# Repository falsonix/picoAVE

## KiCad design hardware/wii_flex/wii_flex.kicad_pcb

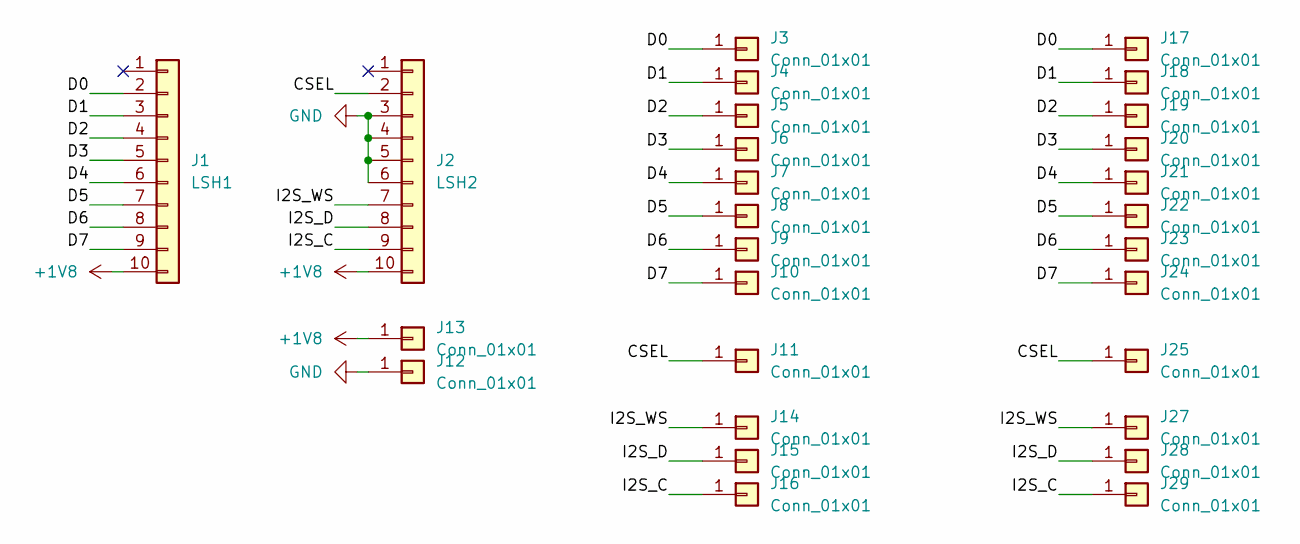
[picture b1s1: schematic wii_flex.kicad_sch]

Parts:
J1: LSH1; PinHeader_1x10_P2.54mm_Vertical
J2: LSH2; PinHeader_1x10_P2.54mm_Vertical
J3, J4, J5, J6, J7, J8, J9, J10, J11, J14, J15, J16, J17, J18, J19, J20, J21, J22, J23, J24, J25, J27, J28, J29: Conn_01x01; wii_pin
J12, J13: Conn_01x01; TestPoint_Pad_2.0x2.0mm

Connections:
+1V8: J1.10, J2.10, J13.1
/CSEL: J2.2, J11.1, J25.1
/D0: J1.2, J3.1, J17.1
/D1: J1.3, J4.1, J18.1
/D2: J1.4, J5.1, J19.1
/D3: J1.5, J6.1, J20.1
/D4: J1.6, J7.1, J21.1
/D5: J1.7, J8.1, J22.1
/D6: J1.8, J9.1, J23.1
/D7: J1.9, J10.1, J24.1
/I2S_C: J2.9, J16.1, J29.1
/I2S_D: J2.8, J15.1, J28.1
/I2S_WS: J2.7, J14.1, J27.1
GND: J2.3, J2.4, J2.5, J2.6, J12.1

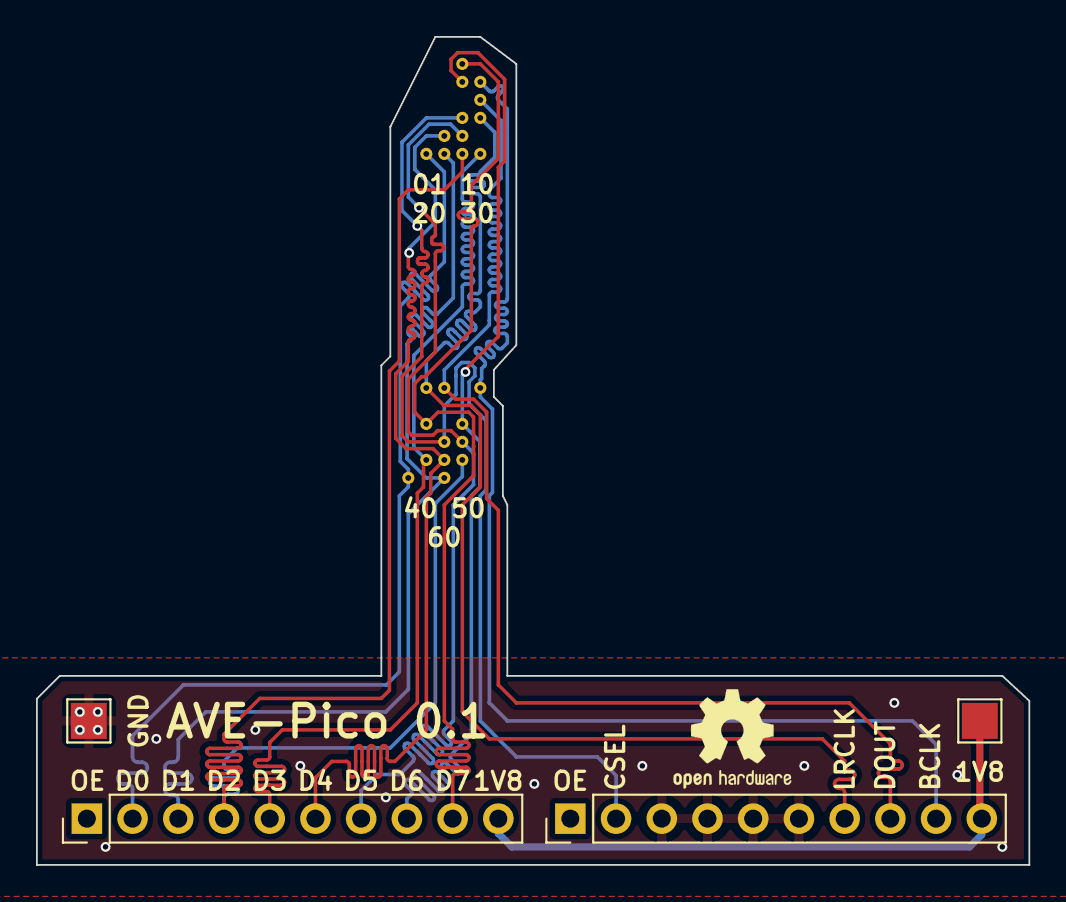
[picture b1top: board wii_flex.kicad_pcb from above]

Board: 2 copper layers, 55.1 x 46.0 mm, 28 parts (0 on the bottom side), 14 nets.

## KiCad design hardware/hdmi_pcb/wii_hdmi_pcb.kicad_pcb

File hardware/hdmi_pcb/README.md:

Adapted from https://github.com/wmi-0/wiihdmi/tree/master/hdmi_pcb/kicad

License: [GPL v3](https://github.com/wmi-0/wiihdmi/blob/master/LICENSE)

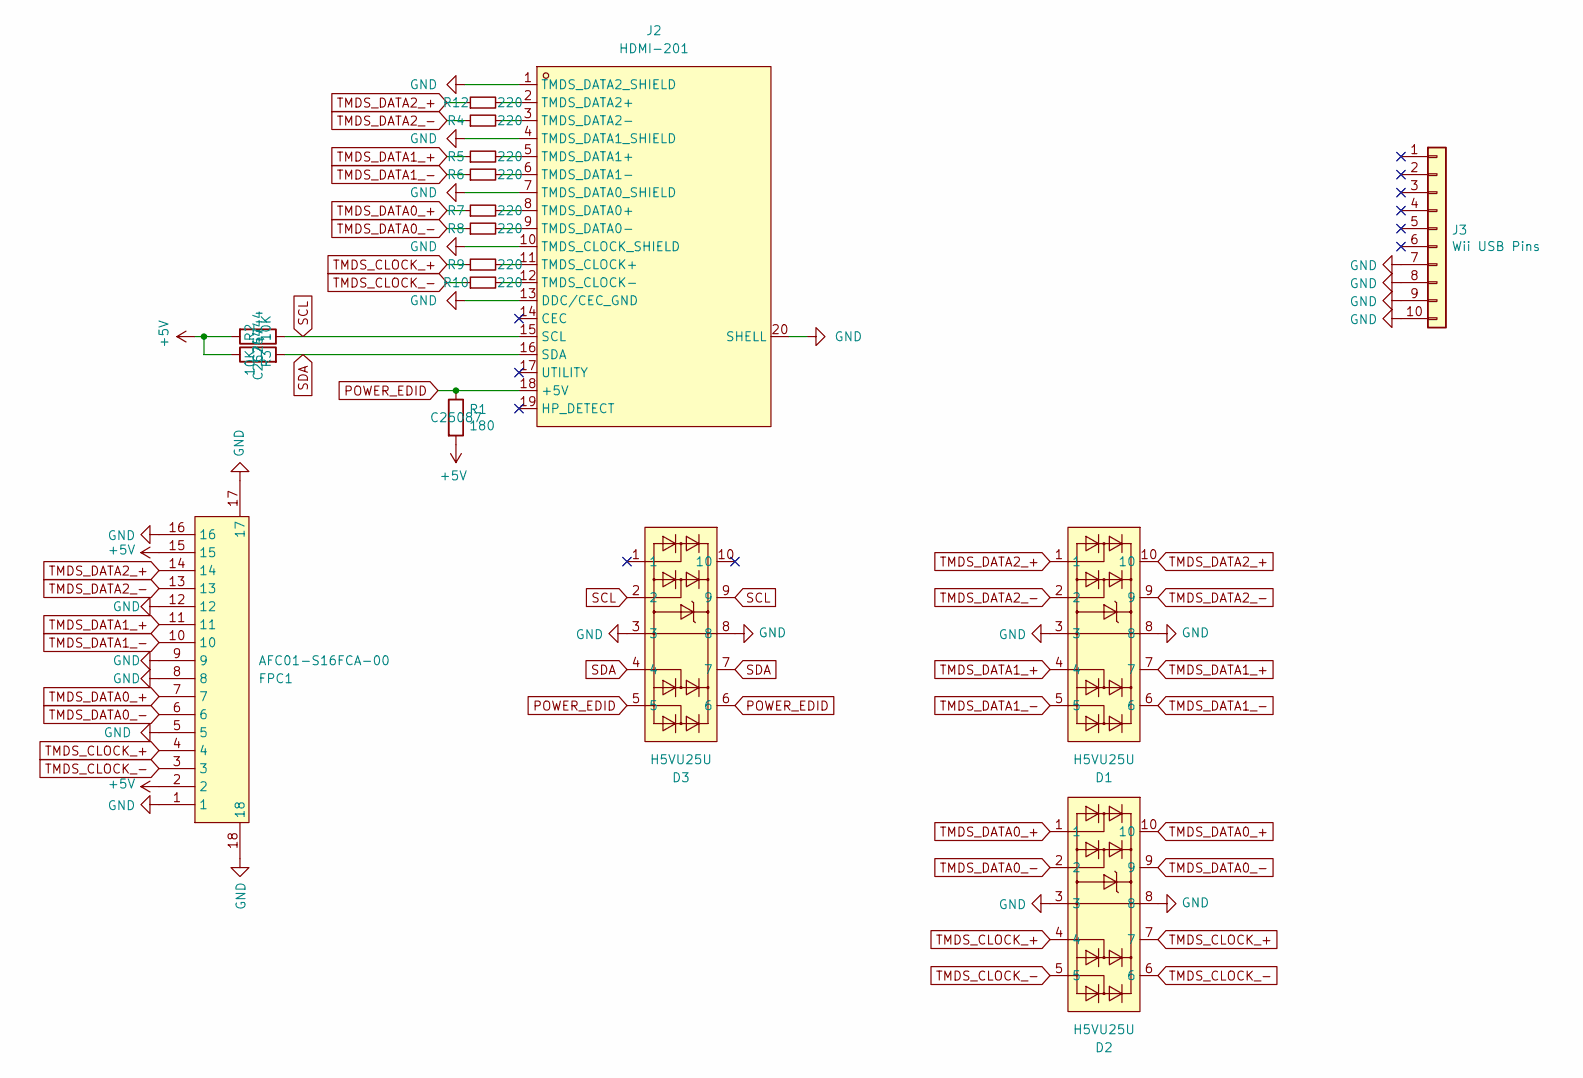
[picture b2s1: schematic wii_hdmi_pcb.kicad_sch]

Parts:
D1, D2, D3: H5VU25U; DFN2510-10_L2.5-W1.0-P0.50-BL; LCSC Part C7420374
FPC1: AFC01-S16FCA-00; FPC-SMD_P0.50-16P_FGS-XJ-H2.0; LCSC Part C262665
J2: HDMI-201; HDMI-SMD_HDMI-201; LCSC Part C720618
J3: Wii USB Pins; Wii USB Port
R1: 180; R_0402_1005Metric; JLC Part C25087
R2, R3: 10K; R_0402_1005Metric; JLC Part C25744
R4, R5, R6, R7, R8, R9, R10, R12: 220; R_0402_1005Metric; JLC Part C25091

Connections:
+5V: FPC1.2, FPC1.15, R1.2, R2.1, R3.2
GND: D1.3, D1.8, D2.3, D2.8, D3.3, D3.8, FPC1.1, FPC1.5, FPC1.8, FPC1.9, FPC1.12, FPC1.16, FPC1.17, FPC1.18, J2.1 (TMDS_DATA2_SHIELD), J2.4 (TMDS_DATA1_SHIELD), J2.7 (TMDS_DATA0_SHIELD), J2.10 (TMDS_CLOCK_SHIELD), J2.13 (DDC/CEC_GND), J2.20 (SHELL), J3.7, J3.8, J3.9, J3.10
unnamed: J2.11 (TMDS_CLOCK+), R9.2
unnamed: J2.12 (TMDS_CLOCK-), R10.2
unnamed: J2.8 (TMDS_DATA0+), R7.2
unnamed: J2.9 (TMDS_DATA0-), R8.2
unnamed: J2.5 (TMDS_DATA1+), R5.2
unnamed: J2.6 (TMDS_DATA1-), R6.2
unnamed: J2.2 (TMDS_DATA2+), R12.2
unnamed: J2.3 (TMDS_DATA2-), R4.2
POWER_EDID: D3.5, D3.6, J2.18 (+5V), R1.1
SCL: D3.2, D3.9, J2.15 (SCL), R3.1
SDA: D3.4, D3.7, J2.16 (SDA), R2.2
TMDS_CLOCK_+: D2.4, D2.7, FPC1.4, R9.1
TMDS_CLOCK_-: D2.5, D2.6, FPC1.3, R10.1
TMDS_DATA0_+: D2.1, D2.10, FPC1.7, R7.1
TMDS_DATA0_-: D2.2, D2.9, FPC1.6, R8.1
TMDS_DATA1_+: D1.4, D1.7, FPC1.11, R5.1
TMDS_DATA1_-: D1.5, D1.6, FPC1.10, R6.1
TMDS_DATA2_+: D1.1, D1.10, FPC1.14, R12.1
TMDS_DATA2_-: D1.2, D1.9, FPC1.13, R4.1

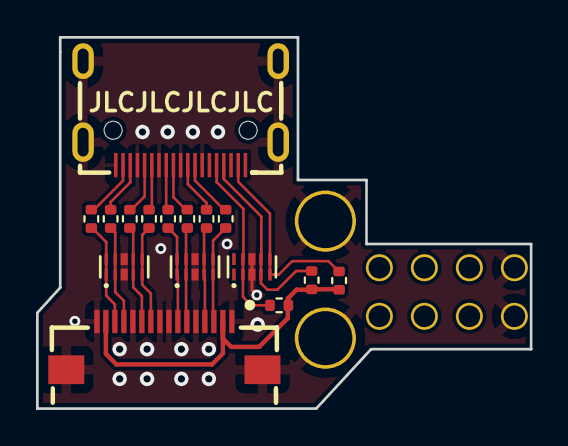
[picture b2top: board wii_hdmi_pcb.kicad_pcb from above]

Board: 2 copper layers, 27.4 x 20.6 mm, 17 parts (0 on the bottom side), 21 nets.

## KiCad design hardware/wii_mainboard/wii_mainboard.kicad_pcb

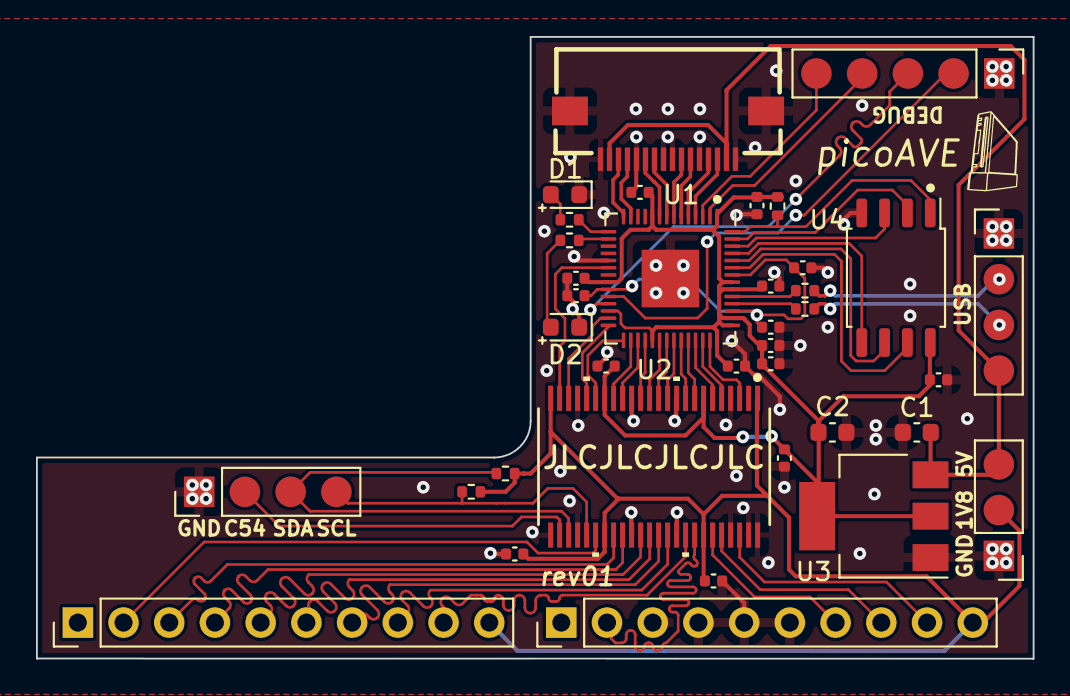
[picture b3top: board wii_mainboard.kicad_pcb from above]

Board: 2 copper layers, 55.4 x 34.5 mm, 37 parts (0 on the bottom side), 61 nets.

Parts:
C1: 10uF; C_0603_1608Metric
C2: 22uF; C_0603_1608Metric
C3, C4, C7, C8, C9, C10, C11, C12, C13, C14, C15, C16, C17: 100nF; C_0402_1005Metric
C5, C6: 1uF; C_0402_1005Metric
D1, D2: LED; LED_0603_1608Metric_plus
FFC1: AFC01-S16FCA-00; FPC-SMD_P0.50-16P_FGS-XJ-H2.0
J1: USB; PinHeader_1x04_P2.54mm_Vertical
J3: Data1; PinHeader_1x10_P2.54mm_Vertical
J4: Data2; PinHeader_1x10_P2.54mm_Vertical
J5: Power; PinHeader_1x03_P2.54mm_Vertical
J6: Data0; PinHeader_1x04_P2.54mm_Vertical
J7: Debug; PinHeader_1x05_P2.54mm_Vertical
R1, R2: 470; R_0402_1005Metric
R3, R6, R7: 10k; R_0402_1005Metric
R4, R5: 33; R_0402_1005Metric
U1: RP2040; QFN-56-1EP_7x7mm_P0.4mm_EP3.2x3.2mm
U2: 74AVC16T245DGGRE; DGG48
U3: AMS1117-3.3; SOT-223-3_TabPin2
U4: W25Q128JVS; SOIC-8_5.23x5.23mm_P1.27mm

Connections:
+1V1: C3.1, C4.1, C5.1, U1.23 (DVDD), U1.45 (VREG_VOUT), U1.50 (DVDD)
+1V8: C16.1, C17.1, J3.10, J4.10, J5.2, R6.1, R7.1, U2.1 (1DIR), U2.24 (2DIR), U2.31 (VCCA), U2.42 (VCCA)
+3V3: C2.1, C6.1, C7.1, C8.1, C9.1, C10.1, C11.1, C12.1, C13.1, C14.1, C15.1, R3.2, U1.1 (IOVDD), U1.10 (IOVDD), U1.22 (IOVDD), U1.26 (RUN), U1.33 (IOVDD), U1.42 (IOVDD), U1.43 (ADC_AVDD), U1.44 (VREG_IN), U1.48 (USB_VDD), U1.49 (IOVDD), U2.7 (VCCB), U2.18 (VCCB), U3.2 (VO), U4.8 (VCC)
+5V: C1.1, FFC1.2, FFC1.15, J1.4, J5.3, U3.3 (VI)
/DVI_0+: FFC1.7, U1.8 (GPIO6)
/DVI_0-: FFC1.6, U1.9 (GPIO7)
/DVI_1+: FFC1.11, U1.6 (GPIO4)
/DVI_1-: FFC1.10, U1.7 (GPIO5)
/DVI_2+: FFC1.14, U1.4 (GPIO2)
/DVI_2-: FFC1.13, U1.5 (GPIO3)
/DVI_C+: FFC1.4, U1.13 (GPIO10)
/DVI_C-: FFC1.3, U1.14 (GPIO11)
/I2C_CLK: U1.28 (GPIO17), U2.20 (2B6)
/I2C_DATA: U1.27 (GPIO16), U2.22 (2B7)
/LED0: R1.2, U1.15 (GPIO12)
/LED1: R2.2, U1.16 (GPIO13)
/LV_I2C_CLK: J6.4, R7.2, U2.29 (2A6)
/LV_I2C_DATA: J6.3, R6.2, U2.27 (2A7)
/LV_WII_54CLK: J6.2, U2.26 (2A8)
/LV_WII_BCLK: J4.9, U2.46 (1A2)
/LV_WII_CSEL: J4.2, U2.41 (1A5)
/LV_WII_D0: J3.2, U2.30 (2A5)
/LV_WII_D1: J3.3, U2.32 (2A4)
/LV_WII_D2: J3.4, U2.33 (2A3)
/LV_WII_D3: J3.5, U2.35 (2A2)
/LV_WII_D4: J3.6, U2.36 (2A1)
/LV_WII_D5: J3.7, U2.37 (1A8)
/LV_WII_D6: J3.8, U2.38 (1A7)
/LV_WII_D7: J3.9, U2.40 (1A6)
/LV_WII_DOUT: J4.8, U2.44 (1A3)
/LV_WII_LRCLK: J4.7, U2.43 (1A4)
/QSPI_SCLK: U1.52 (QSPI_SCLK), U4.6 (CLK)
/QSPI_SD0: U1.53 (QSPI_SD0), U4.5 (DI(IO0))
/QSPI_SD1: U1.55 (QSPI_SD1), U4.2 (DO(IO1))
/QSPI_SD2: U1.54 (QSPI_SD2), U4.3 (IO2)
/QSPI_SD3: U1.51 (QSPI_SD3), U4.7 (IO3)
/QSPI_SS: R3.1, U1.56 (QSPI_SS), U4.1 (~CS)
/RX: J7.5, U1.3 (GPIO1)
/SWCLK: J7.2, U1.24 (SWCLK)
/SWD: J7.3, U1.25 (SWD)
/TX: J7.4, U1.2 (GPIO0)
/USB_D+: J1.2, R4.1
/USB_D-: J1.3, R5.1
/WII_54CLK: U1.20 (XIN), U2.23 (2B8)
/WII_BCLK: U1.41 (GPIO29_ADC3), U2.3 (1B2)
/WII_CSEL: U1.38 (GPIO26_ADC0), U2.8 (1B5)
/WII_D0: U1.29 (GPIO18), U2.19 (2B5)
/WII_D1: U1.30 (GPIO19), U2.17 (2B4)
/WII_D2: U1.31 (GPIO20), U2.16 (2B3)
/WII_D3: U1.32 (GPIO21), U2.14 (2B2)
/WII_D4: U1.34 (GPIO22), U2.13 (2B1)
/WII_D5: U1.35 (GPIO23), U2.12 (1B8)
/WII_D6: U1.36 (GPIO24), U2.11 (1B7)
/WII_D7: U1.37 (GPIO25), U2.9 (1B6)
/WII_DOUT: U1.40 (GPIO28_ADC2), U2.5 (1B3)
/WII_LRCLK: U1.39 (GPIO27_ADC1), U2.6 (1B4)
GND: C1.2, C2.2, C3.2, C4.2, C5.2, C6.2, C7.2, C8.2, C9.2, C10.2, C11.2, C12.2, C13.2, C14.2, C15.2, C16.2, C17.2, D1.1 (K), D2.1 (K), FFC1.1, FFC1.5, FFC1.8, FFC1.9, FFC1.12, FFC1.16, FFC1.17, FFC1.18, J1.1, J4.3, J4.4, J4.5, J4.6, J5.1, J6.1, J7.1, U1.19 (TESTEN), U1.57 (GND), U2.4 (GND), U2.10 (GND), U2.15 (GND), U2.21 (GND), U2.25 (*2OE), U2.28 (GND), U2.34 (GND), U2.39 (GND), U2.45 (GND), U2.47 (1A1), U2.48 (*1OE), U3.1 (GND), U4.4 (GND)
unnamed: D1.2 (A), R1.1
unnamed: D2.2 (A), R2.1
unnamed: R5.2, U1.46 (USB_DM)
unnamed: R4.2, U1.47 (USB_DP)

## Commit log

2025-01-12 Add section about ordering and assembly
2025-01-12 PCB project files
2025-06-11 Create README.md and production_gerbers directory
2025-06-11 add gerber files
